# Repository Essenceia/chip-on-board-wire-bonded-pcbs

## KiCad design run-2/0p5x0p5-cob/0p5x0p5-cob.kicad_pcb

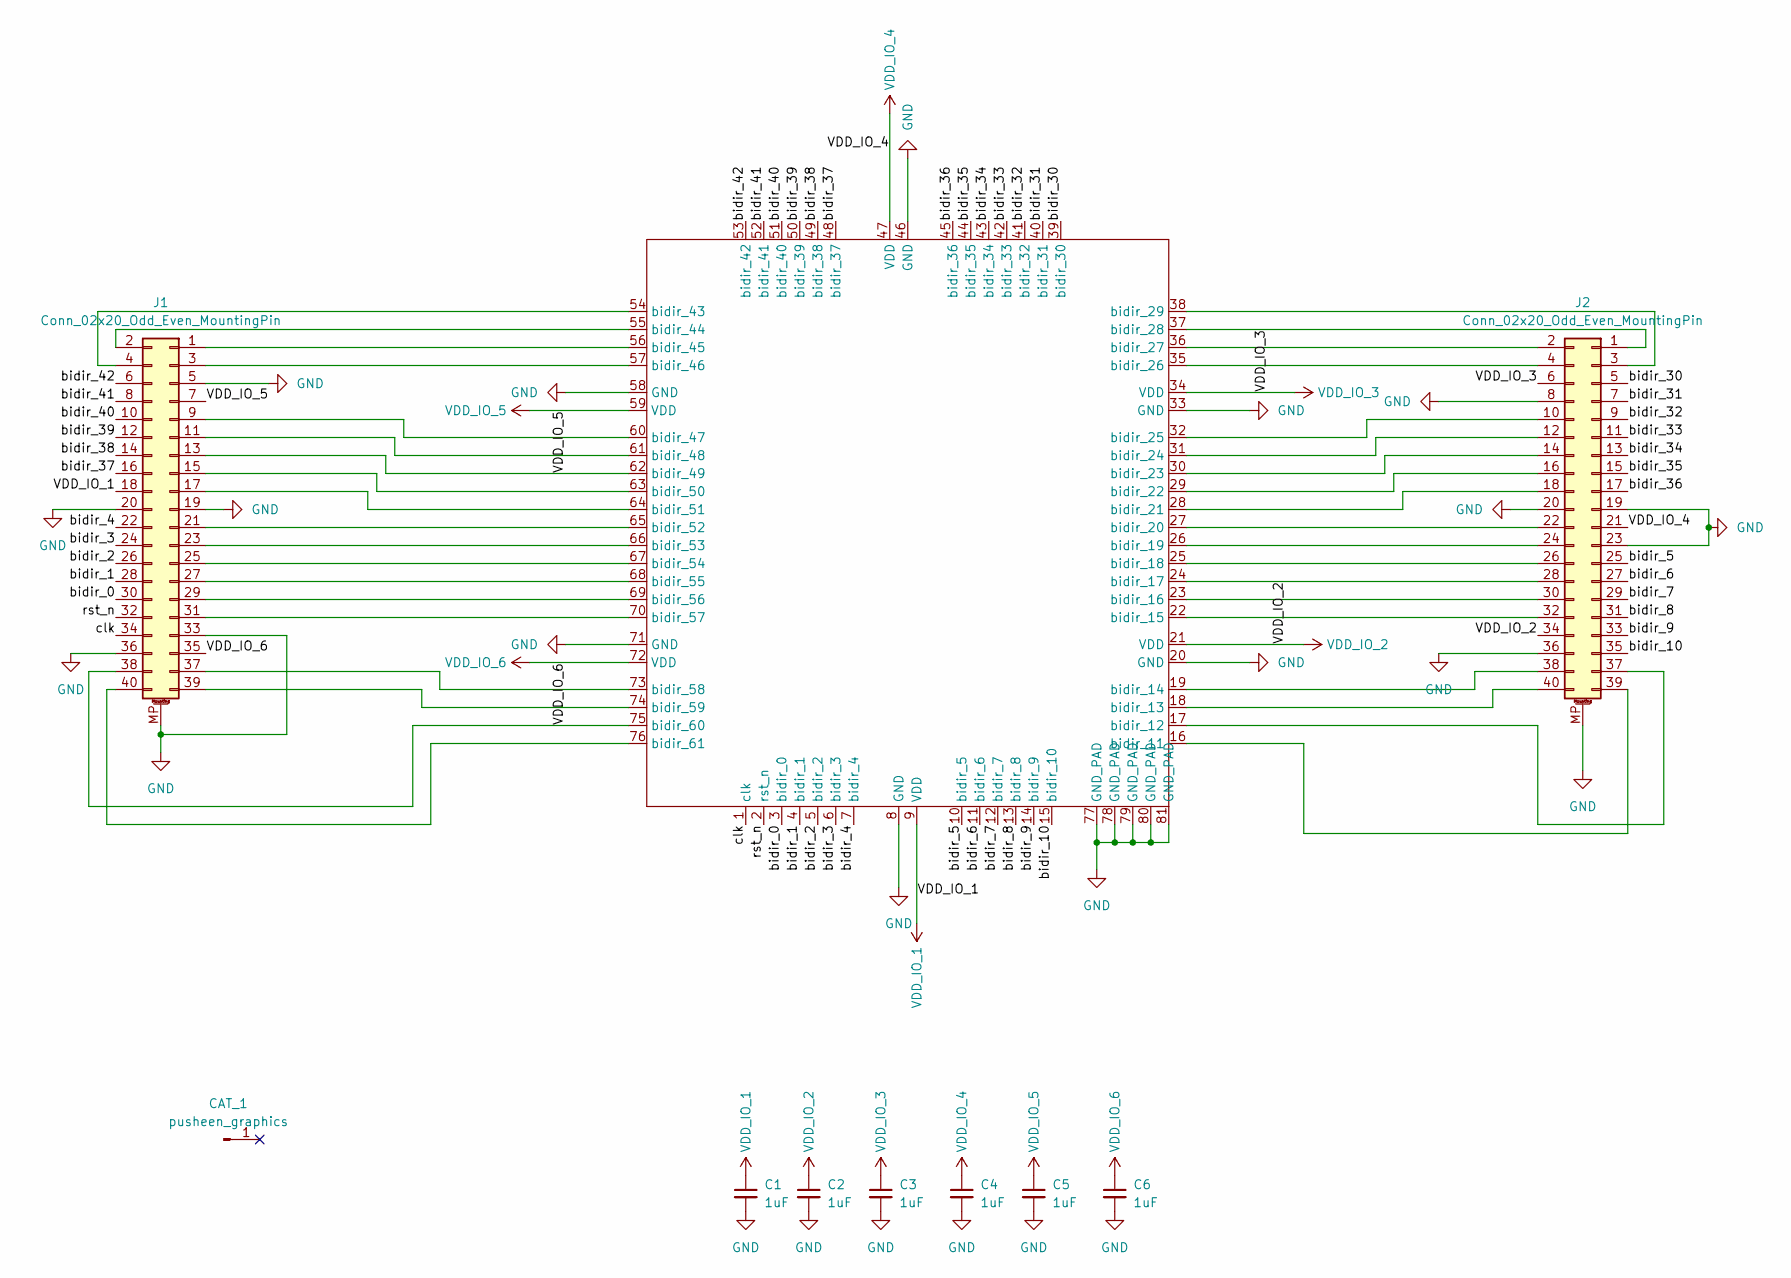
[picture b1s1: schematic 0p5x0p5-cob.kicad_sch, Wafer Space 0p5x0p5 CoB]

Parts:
C1, C2, C3, C4, C5, C6: 1uF; C_0201_0603Metric
CAT_1: pusheen_graphics; pusheen_back
J1, J2: Conn_02x20_Odd_Even_MountingPin; Hirose_DF40C-40DP-0.4V_2x20-1MP_P0.4mm
U1: waferspace_p5xp5_padring_staggered

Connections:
/bidir_0: J1.30, U1.3 (bidir_0)
/bidir_1: J1.28, U1.4 (bidir_1)
/bidir_2: J1.26, U1.5 (bidir_2)
/bidir_3: J1.24, U1.6 (bidir_3)
/bidir_4: J1.22, U1.7 (bidir_4)
/bidir_5: J2.25, U1.10 (bidir_5)
/bidir_6: J2.27, U1.11 (bidir_6)
/bidir_7: J2.29, U1.12 (bidir_7)
/bidir_8: J2.31, U1.13 (bidir_8)
/bidir_9: J2.33, U1.14 (bidir_9)
/bidir_10: J2.35, U1.15 (bidir_10)
/bidir_30: J2.5, U1.39 (bidir_30)
/bidir_31: J2.7, U1.40 (bidir_31)
/bidir_32: J2.9, U1.41 (bidir_32)
/bidir_33: J2.11, U1.42 (bidir_33)
/bidir_34: J2.13, U1.43 (bidir_34)
/bidir_35: J2.15, U1.44 (bidir_35)
/bidir_36: J2.17, U1.45 (bidir_36)
/bidir_37: J1.16, U1.48 (bidir_37)
/bidir_38: J1.14, U1.49 (bidir_38)
/bidir_39: J1.12, U1.50 (bidir_39)
/bidir_40: J1.10, U1.51 (bidir_40)
/bidir_41: J1.8, U1.52 (bidir_41)
/bidir_42: J1.6, U1.53 (bidir_42)
/clk: J1.34, U1.1 (clk)
/rst_n: J1.32, U1.2 (rst_n)
GND: C1.2, C2.2, C3.2, C4.2, C5.2, C6.2, J1.5, J1.19, J1.20, J1.33, J1.36, J1.MP (MountPin), J2.8, J2.19, J2.20, J2.23, J2.36, J2.MP (MountPin), U1.8 (GND), U1.20 (GND), U1.33 (GND), U1.46 (GND), U1.58 (GND), U1.71 (GND), U1.77 (GND_PAD), U1.78 (GND_PAD), U1.79 (GND_PAD), U1.80 (GND_PAD), U1.81 (GND_PAD)
unnamed: J1.1, U1.56 (bidir_45)
unnamed: J1.2, U1.55 (bidir_44)
unnamed: J1.3, U1.57 (bidir_46)
unnamed: J1.4, U1.54 (bidir_43)
unnamed: J1.9, U1.60 (bidir_47)
unnamed: J1.11, U1.61 (bidir_48)
unnamed: J1.13, U1.62 (bidir_49)
unnamed: J1.15, U1.63 (bidir_50)
unnamed: J1.17, U1.64 (bidir_51)
unnamed: J1.21, U1.65 (bidir_52)
unnamed: J1.23, U1.66 (bidir_53)
unnamed: J1.25, U1.67 (bidir_54)
unnamed: J1.27, U1.68 (bidir_55)
unnamed: J1.29, U1.69 (bidir_56)
unnamed: J1.31, U1.70 (bidir_57)
unnamed: J1.37, U1.73 (bidir_58)
unnamed: J1.38, U1.75 (bidir_60)
unnamed: J1.39, U1., U1.74 (bidir_59)
unnamed: J1.40, U1.76 (bidir_61)
unnamed: J2.1, U1.37 (bidir_28)
unnamed: J2.2, U1.36 (bidir_27)
unnamed: J2.3, U1.38 (bidir_29)
unnamed: J2.4, U1.35 (bidir_26)
unnamed: J2.10, U1.32 (bidir_25)
unnamed: J2.12, U1.31 (bidir_24)
unnamed: J2.14, U1.30 (bidir_23)
unnamed: J2.16, U1.29 (bidir_22)
unnamed: J2.18, U1.28 (bidir_21)
unnamed: J2.22, U1.27 (bidir_20)
unnamed: J2.24, U1.26 (bidir_19)
unnamed: J2.26, U1.25 (bidir_18)
unnamed: J2.28, U1.24 (bidir_17)
unnamed: J2.30, U1.23 (bidir_16)
unnamed: J2.32, U1.22 (bidir_15)
unnamed: J2.37, U1.17 (bidir_12)
unnamed: J2.38, U1.19 (bidir_14)
unnamed: J2.39, U1.16 (bidir_11)
unnamed: J2.40, U1.18 (bidir_13)
VDD_IO_1: C1.1, J1.18, U1.9 (VDD)
VDD_IO_2: C2.1, J2.34, U1.21 (VDD)
VDD_IO_3: C3.1, J2.6, U1.34 (VDD)
VDD_IO_4: C4.1, J2.21, U1.47 (VDD)
VDD_IO_5: C5.1, J1.7, U1.59 (VDD)
VDD_IO_6: C6.1, J1.35, U1.72 (VDD)

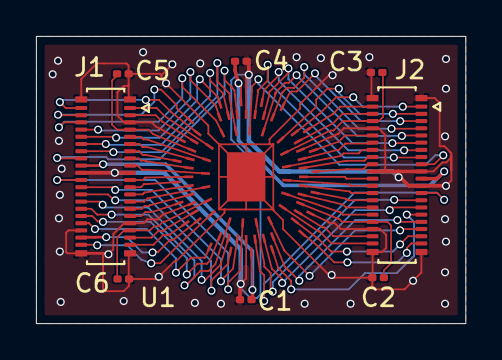
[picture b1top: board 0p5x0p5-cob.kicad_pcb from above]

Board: 2 copper layers, 23.8 x 16.0 mm, 10 parts (1 on the bottom side), 71 nets.
